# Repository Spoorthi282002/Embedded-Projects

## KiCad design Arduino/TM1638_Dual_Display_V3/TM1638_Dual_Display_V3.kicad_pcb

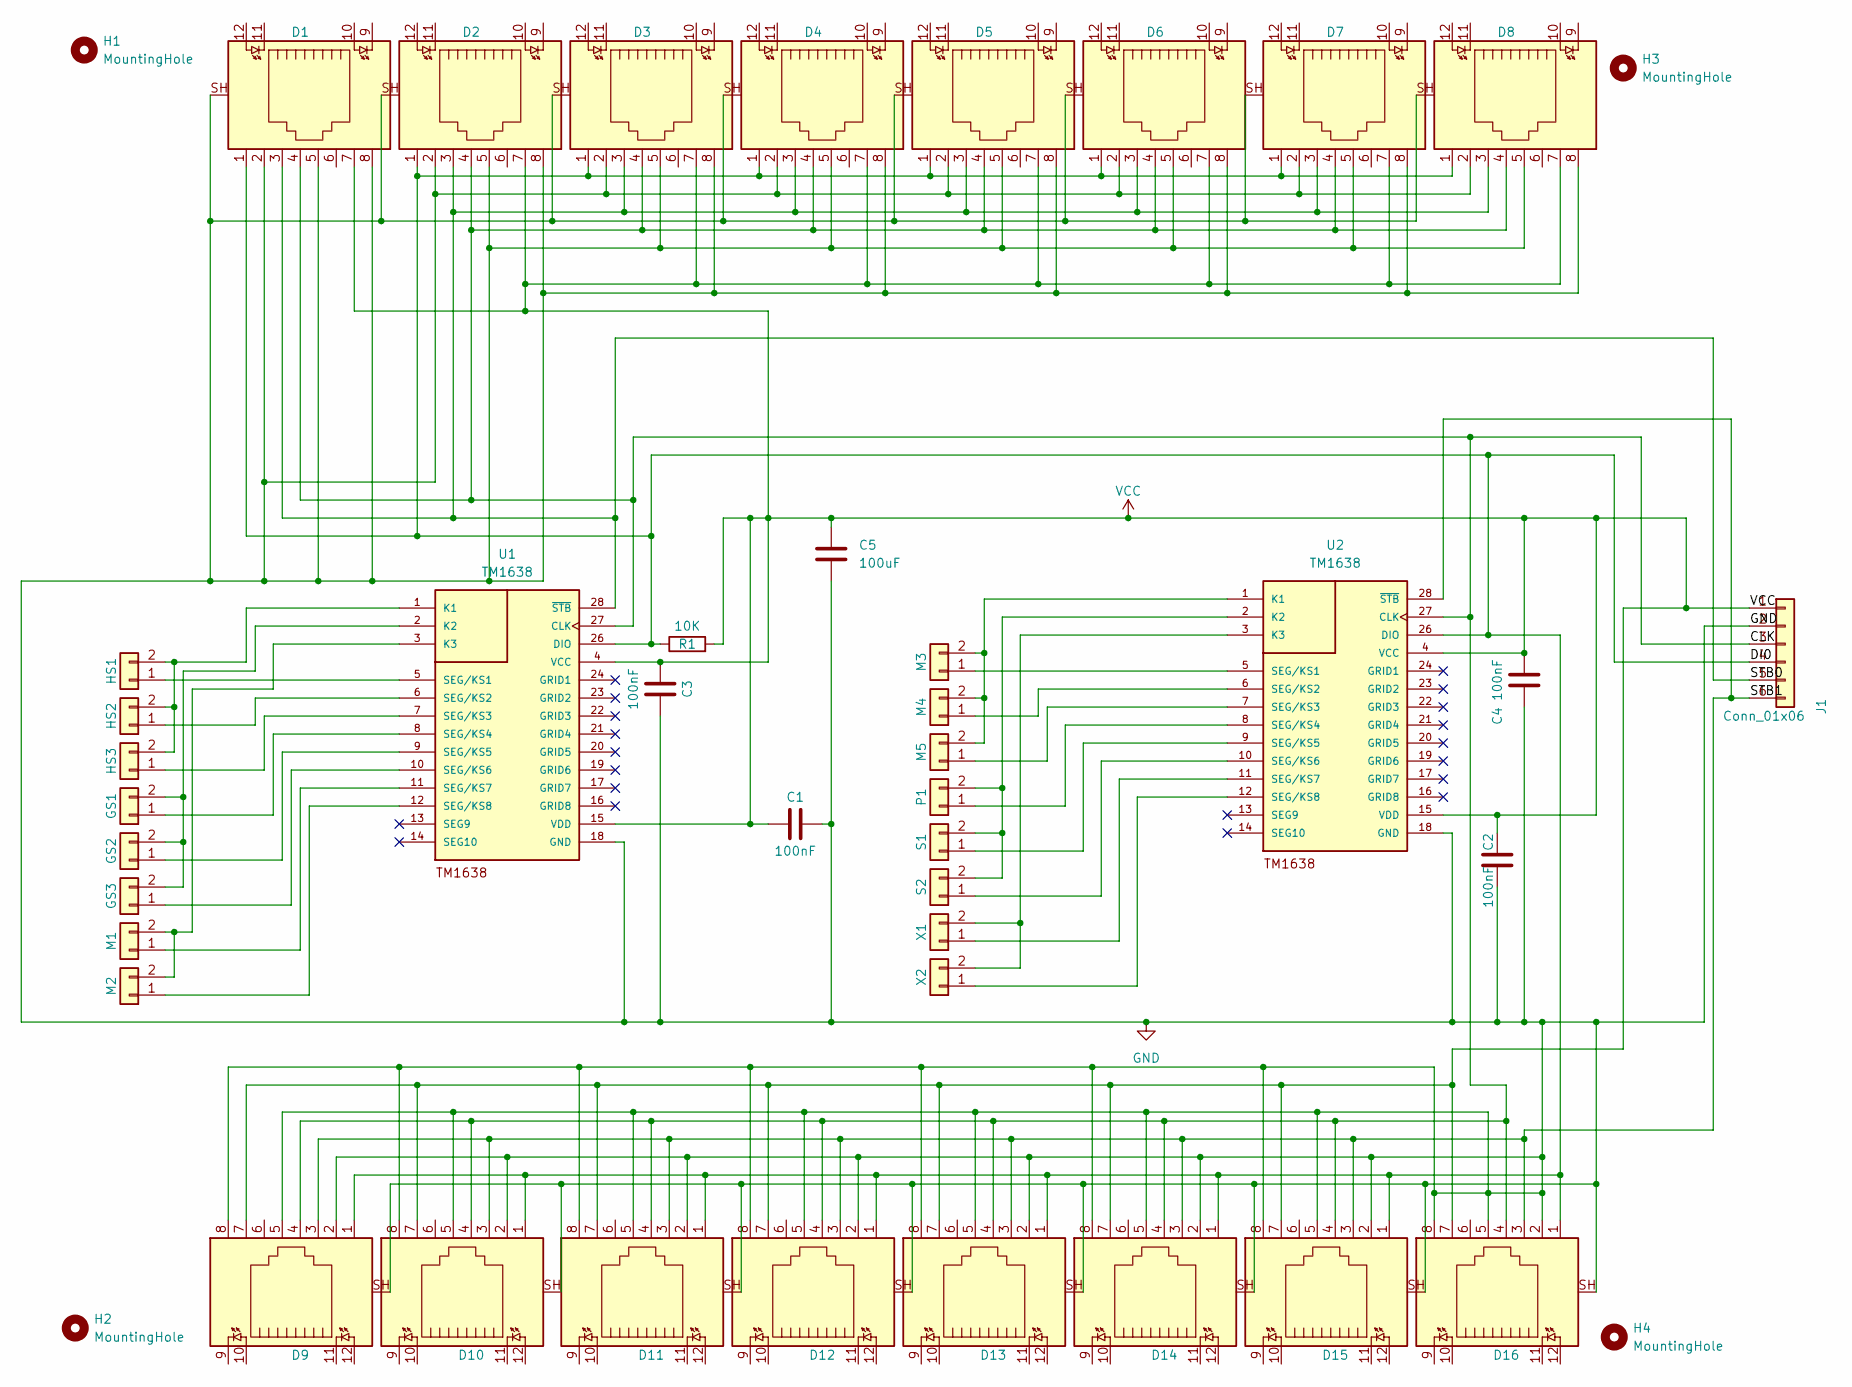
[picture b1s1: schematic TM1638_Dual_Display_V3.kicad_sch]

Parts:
C1, C2, C3, C4: 100nF; C_0603_1608Metric
C5: 100uF; C_0603_1608Metric
D1, D2, D3, D4, D5, D6, D7, D8, D9, D10, D11, D12, D13, D14, D15, D16: RJ45_LED_Shielded; RJ45_Hanrun_HR911105A_Horizontal
GS1, GS2, GS3: Conn_01x02; PinSocket_1x02_P2.54mm_Vertical
H1, H2, H3, H4: MountingHole; MountingHole_3.2mm_M3
HS1, HS2, HS3: Conn_01x02; PinSocket_1x02_P2.54mm_Vertical
J1: Conn_01x06; PinSocket_1x06_P2.54mm_Vertical
M1, M2, M3, M4, M5: Conn_01x02; PinSocket_1x02_P2.54mm_Vertical
P1: Conn_01x02; PinSocket_1x02_P2.54mm_Vertical
R1: 10K; R_0603_1608Metric
S1, S2: Conn_01x02; PinSocket_1x02_P2.54mm_Vertical
U1, U2: TM1638; SOIC127P1041X265-28N
X1, X2: Conn_01x02; PinSocket_1x02_P2.54mm_Vertical

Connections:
/CLK: D1.4, D2.4, D3.4, D4.4, D5.4, D6.4, D7.4, D8.4, D9.4, D10.4, D11.4, D12.4, D13.4, D14.4, D15.4, D16.4, J1.3, U1.27 (CLK), U2.27 (CLK)
/DI0: D1.1, D2.1, D3.1, D4.1, D5.1, D6.1, D7.1, D8.1, D9.1, D10.1, D11.1, D12.1, D13.1, D14.1, D15.1, D16.1, J1.4, R1.1, U1.26 (DIO), U2.26 (DIO)
/STB0: D1.3, D2.3, D3.3, D4.3, D5.3, D6.3, D7.3, D8.3, J1.5, U1.28 (~STB)
/STB1: D9.3, D10.3, D11.3, D12.3, D13.3, D14.3, D15.3, D16.3, J1.6, U2.28 (~STB)
GND: C1.1, C2.1, C3.2, C4.1, C5.2, D1.2, D1.5, D1.8, D1.SH, D2.2, D2.5, D2.8, D2.SH, D3.2, D3.5, D3.8, D3.SH, D4.2, D4.5, D4.8, D4.SH, D5.2, D5.5, D5.8, D5.SH, D6.2, D6.5, D6.8, D6.SH, D7.2, D7.5, D7.8, D7.SH, D8.2, D8.5, D8.8, D8.SH, D9.2, D9.5, D9.8, D9.SH, D10.2, D10.5, D10.8, D10.SH, D11.2, D11.5, D11.8, D11.SH, D12.2, D12.5, D12.8, D12.SH, D13.2, D13.5, D13.8, D13.SH, D14.2, D14.5, D14.8, D14.SH, D15.2, D15.5, D15.8, D15.SH, D16.2, D16.5, D16.8, D16.SH, J1.2, U1.18 (GND), U1.25 (GND), U2.18 (GND), U2.25 (GND)
unnamed: GS1.1, U1.8 (SEG/KS4)
unnamed: GS1.2, GS2.2, GS3.2, U1.2 (K2)
unnamed: GS2.1, U1.9 (SEG/KS5)
unnamed: GS3.1, U1.10 (SEG/KS6)
unnamed: HS1.1, U1.5 (SEG/KS1)
unnamed: HS1.2, HS2.2, HS3.2, U1.1 (K1)
unnamed: HS2.1, U1.6 (SEG/KS2)
unnamed: HS3.1, U1.7 (SEG/KS3)
unnamed: M1.1, U1.11 (SEG/KS7)
unnamed: M1.2, M2.2, U1.3 (K3)
unnamed: M2.1, U1.12 (SEG/KS8)
unnamed: M3.1, U2.5 (SEG/KS1)
unnamed: M3.2, M4.2, M5.2, U2.1 (K1)
unnamed: M4.1, U2.6 (SEG/KS2)
unnamed: M5.1, U2.7 (SEG/KS3)
unnamed: P1.1, U2.8 (SEG/KS4)
unnamed: P1.2, S1.2, S2.2, U2.2 (K2)
unnamed: S1.1, U2.9 (SEG/KS5)
unnamed: S2.1, U2.10 (SEG/KS6)
unnamed: U2.3 (K3), X1.2, X2.2
unnamed: U2.11 (SEG/KS7), X1.1
unnamed: U2.12 (SEG/KS8), X2.1
VCC: C1.2, C2.2, C3.1, C4.2, C5.1, D1.7, D2.7, D3.7, D4.7, D5.7, D6.7, D7.7, D8.7, D9.7, D10.7, D11.7, D12.7, D13.7, D14.7, D15.7, D16.7, J1.1, R1.2, U1.4 (VCC), U1.15 (VDD), U2.4 (VCC), U2.15 (VDD)

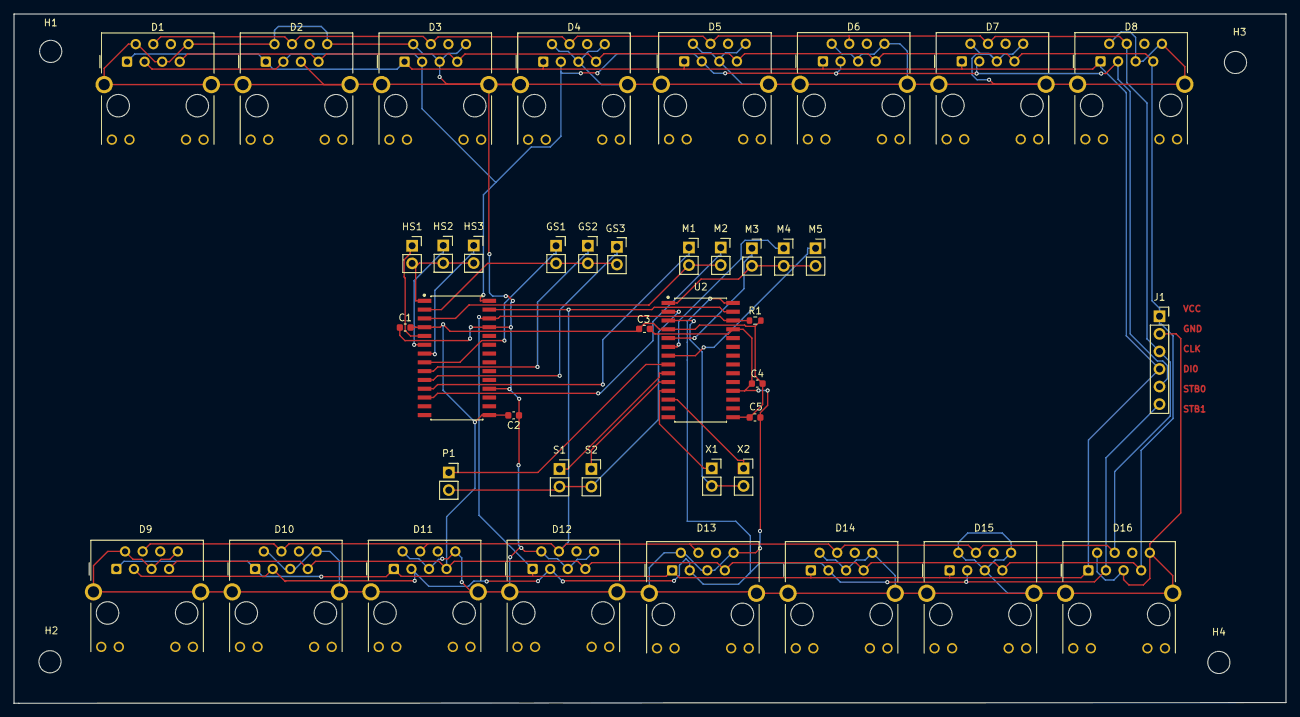
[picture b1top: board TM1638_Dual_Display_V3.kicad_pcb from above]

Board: 2 copper layers, 183.8 x 99.6 mm, 45 parts (0 on the bottom side), 28 nets.
